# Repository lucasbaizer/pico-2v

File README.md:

# Pico 2V

Pico 2V is an [RP2350](https://www.raspberrypi.com/products/rp2350) development board that is (mostly) pin-compatible with the official [Raspberry Pi Pico 2](https://www.raspberrypi.com/products/raspberry-pi-pico-2) board, but with some additional features and changes:

* Switchable 3.3V/1.8V GPIOs: the official Pico 2 only supports running at 3.3V. Pico 2V has a jumper that lets you select between 3.3V and 1.8V.
* QSPI breakout: the official Pico 2 has an RP2350A as the chip, with on-board flash wired to the RP2350A's QSPI interface. Pico 2V has on RP2354A instead, which has 2MiB on-chip flash. As such, the RP2354A's QSPI interface on Pico 2V is broken out into two headers that can fit an [SOIC-8 breakout board](https://www.amazon.com/dp/B0DQKZG7TH) or be wired to some part of your breadboard. This allows you to write firmware that can communicate with QSPI flash using all 4 data lanes.
* On-board reset button.
* Powered-on indicator LED.
* USB-C receptacle instead of the Micro-B receptacle used on the official Pico 2.
* [10-pin Cortex Debug](https://developer.arm.com/documentation/101416/0100/Hardware-Description/Target-Interfaces/Cortex-Debug--10-pin-) connector instead of the [Raspberry Pi 3-pin Debug](https://pip-assets.raspberrypi.com/categories/885-raspberry-pi-debug-probe/documents/RP-008189-DS-1-debug-connector-specification.pdf?disposition=inline) connector used on the official Pico 2.

## Board Rendering and Pinout

* The GPIO pin headers are pin-compatible with [the official Pico 2](https://www.raspberrypi.com/documentation/microcontrollers/images/pico-2-r4-pinout.svg), and the dimensions of Pico 2V are the same as the official Pico 2, so you can easily swap out an existing Pico 2 on your breadboard for a Pico 2V. However, note that the `3V3(OUT)` pin is actually the output of the selected voltage, so it is instead a `VDD(OUT)` pin, which is only powered when a jumper is fitted to the voltage selector header. Additionally, the `3V3_EN` pin is left floating on Pico 2V.
* GPIO29 (which is not broken out/usable on the official Pico 2) is wired to an on-board voltage comparator, so you can detect from your firmware whether the RP2354A is operating at 3.3V or 1.8V by reading the value of GPIO29 (GPIO29 logic level high indicates 3.3V, logic level low indicates 1.8V). 
* The user LED is connected to GPIO25, just like on the official Pico 2.
* Pressing the `RESET` button will tie the `RUN` pin to ground.
* The QSPI pinout is as follows:
  * Pin 1: `SS` (note that pressing the `BOOTSEL` button will tie this to ground, even after the bootrom exits -- this is a fundamental constraint of how the RP235x bootrom works).
  * Pin 2: `SD1`/`MISO`
  * Pin 3: `SD2`
  * Pin 4: `GND`
  * Pin 5: `VDD` (voltage determined by voltage selection jumper)
  * Pin 6: `SD3`
  * Pin 7: `SCLK`
  * Pin 8: `SD0`/`MOSI`
  * Note that the pin numbering convention here is different from the standard SOIC-8 pin numbering convention. This is a bug with the labeling on the PCB (the '5' and '8' markers should be swapped on the PCB) that will be fixed in rev 1. However, the positions of the pins themselves does match the SOIC-8 layout; the issue is simply in the labeling of the numbers on the PCB.

## How can I buy a Pico 2V?

Fabrication exports are in the `fab/rev0` directory. I had the board produced by [JLCPCB](https://jlcpcb.com). To have JLCPCB produce some boards for you to have, zip all the files in the `fab/rev0` directory and provide the ZIP file to JLCPCB. I used Lead-Free HASL as the surface finish and a PCB thickness of 1mm. If you want them to assembly the components onto the board as well, provide them the BOM and CPL files in `fab/rev0/smt/pico-2v-bom.xls` and `fab/rev0/smt/pico-2v-all-pos.csv` respectively. Note that the GPIO and QSPI headers are not included in the BOM file, but the voltage selection header is; you can select or remove these as you desire.

## Goals for Future Revisions

* Swap the '5' and '8' markers on the QSPI breakout pins.
* Separate voltage selection jumper for QSPI.
* Two more on-board LEDs (since GPIOs 23 and 24 were left unused in rev 0).

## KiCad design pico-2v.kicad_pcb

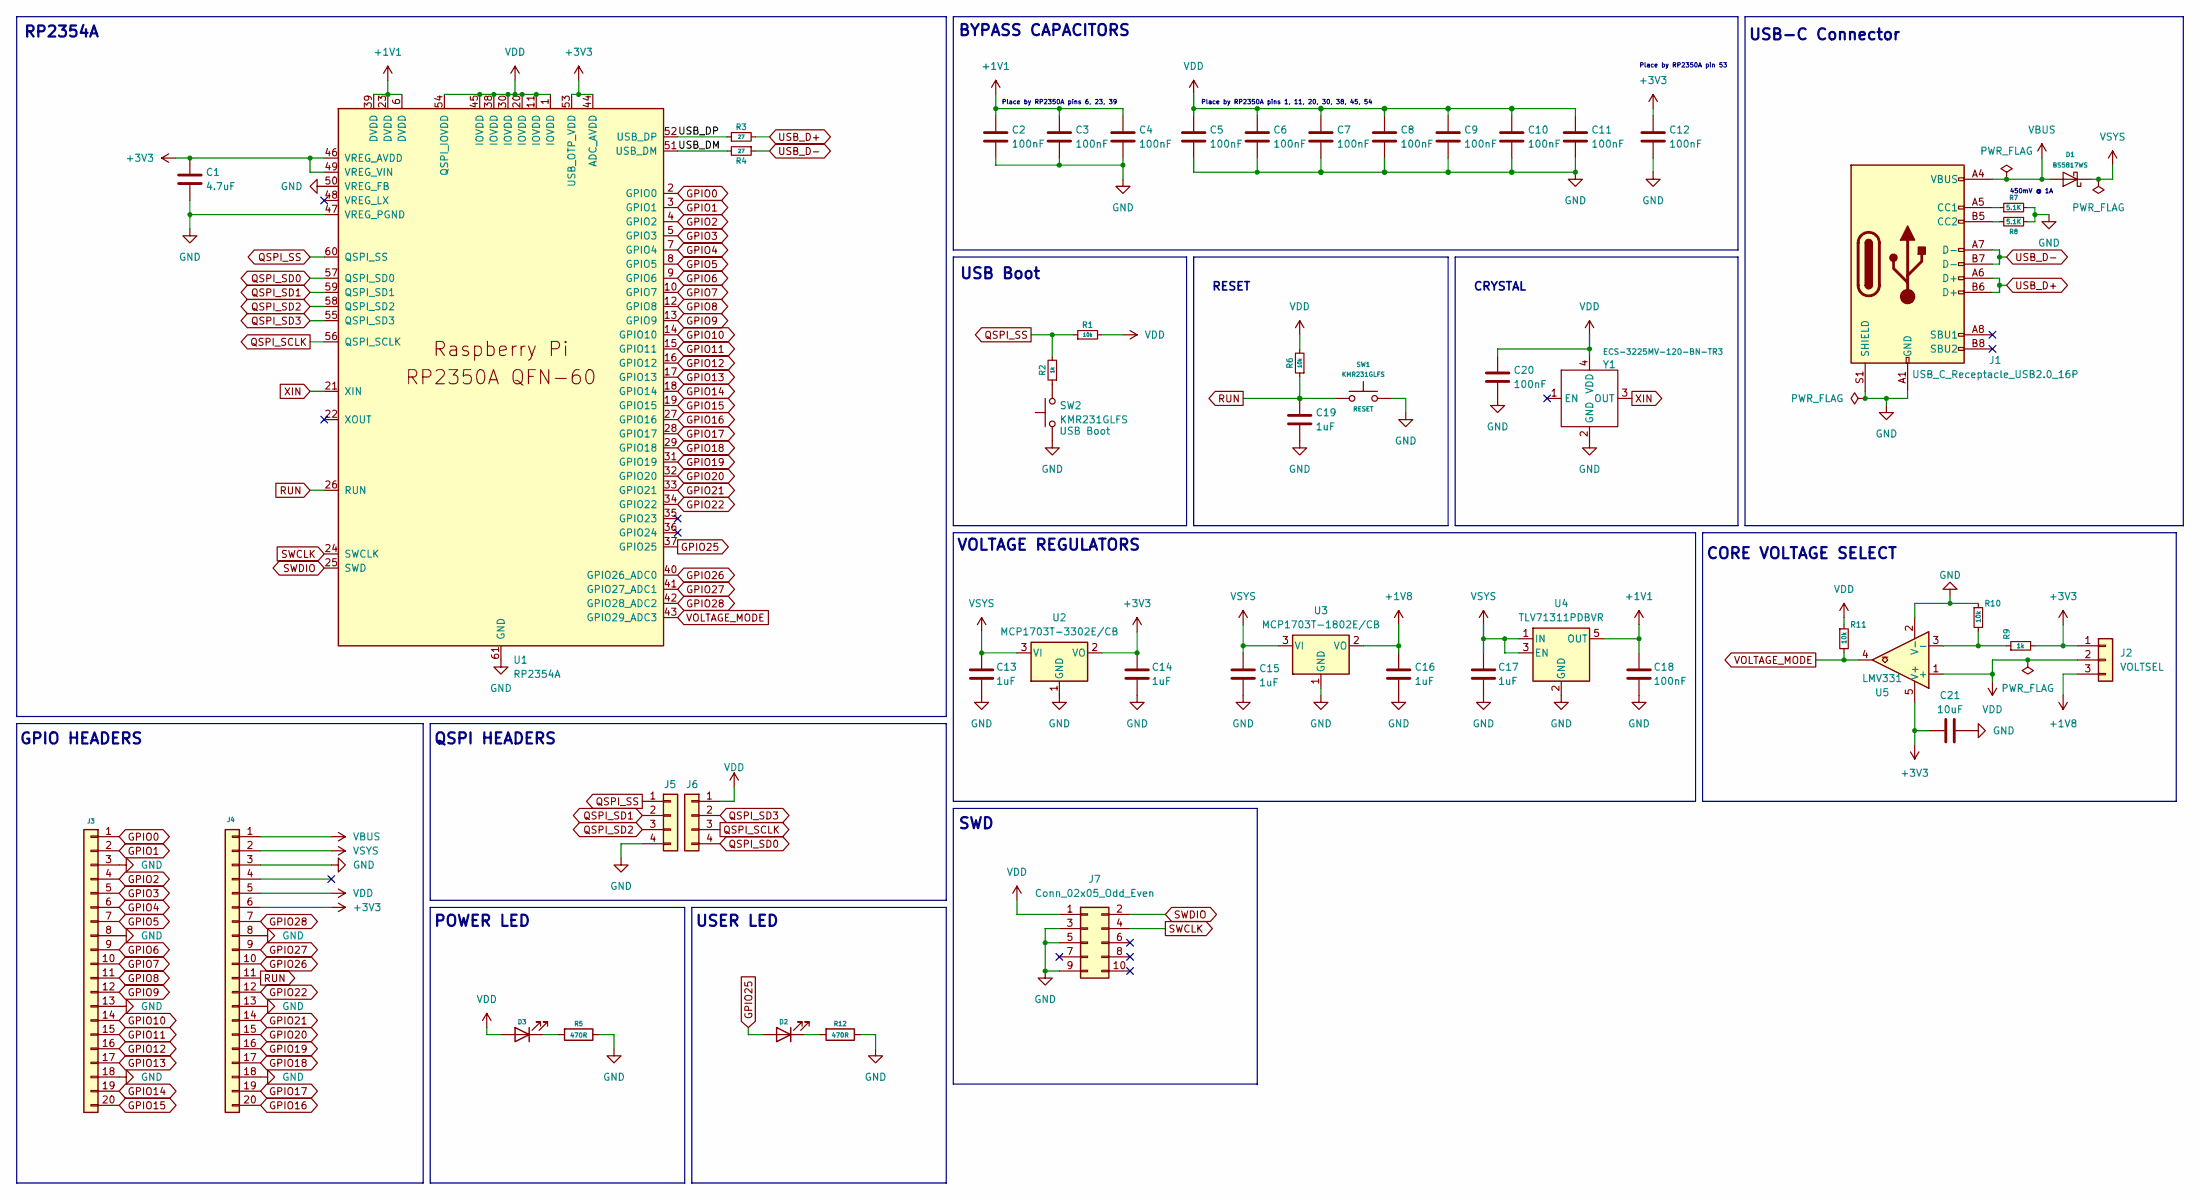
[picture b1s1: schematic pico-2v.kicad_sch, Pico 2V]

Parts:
C1: 4.7uF; C_0402_1005Metric
C2, C3, C4, C5, C6, C7, C8, C9, C10, C11, C12, C18, C20: 100nF; C_0402_1005Metric
C13, C14, C15, C16, C17, C19: 1uF; C_0402_1005Metric
C21: 10uF; C_0402_1005Metric
D1: BS5817WS; D_SOD-323_HandSoldering; MPN B5817WS
D2, D3: RED; LED_0603_1608Metric; MPN 19-21SURC/S530-A2/TR8
J1: USB_C_Receptacle_USB2.0_16P; USB_C_Receptacle_HRO_TYPE-C-31-M-12
J2: VOLTSEL; PinHeader_1x03_P2.54mm_Vertical
J3: Header-1; PinHeader_1x20_P2.54mm_Vertical; MPN DNP
J4: Header-2; PinHeader_1x20_P2.54mm_Vertical; MPN DNP
J5, J6: Conn_01x04; PinHeader_1x04_P2.54mm_Vertical
J7: Conn_02x05_Odd_Even; PinHeader_2x05_P1.27mm_Vertical_SMD
R1, R6, R10, R11: 10k; R_0402_1005Metric
R2, R9: 1k; R_0402_1005Metric
R3, R4: 27; R_0402_1005Metric
R5, R12: 470R; R_0402_1005Metric; MPN WR04X4700FTL
R7, R8: 5.1K; R_0402_1005Metric; MPN WR04X5101FTL
SW1: KMR231GLFS; SW_Push_1P1T_NO_CK_KMR2; MPN UK-B0273-SP25Y
SW2: KMR231GLFS; SW_Push_1P1T_NO_CK_KMR2
U1: RP2354A; RP2350A-QFN-60-1EP_7x7_P0.4mm_EP3.4x3.4mm_ThermalVias
U2: MCP1703T-3302E/CB; SOT-23
U3: MCP1703T-1802E/CB; SOT-23
U4: TLV71311PDBVR; SOT-23-5
U5: LMV331; SOT-353_SC-70-5
Y1: ECS-3225MV-120-BN-TR3

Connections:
+1V1: C2.1, C3.1, C4.1, C18.1, U1.6 (DVDD), U1.23 (DVDD), U1.39 (DVDD), U4.5 (OUT)
+1V8: C16.1, J2.3, U3.2 (VO)
+3V3: C1.1, C12.1, C14.1, C21.1, J2.1, J4.6, R9.2, U1.44 (ADC_AVDD), U1.46 (VREG_AVDD), U1.49 (VREG_VIN), U1.53 (USB_OTP_VDD), U2.2 (VO), U5.5 (V+)
/USB_DM: R4.2, U1.51 (USB_DM)
/USB_DP: R3.1, U1.52 (USB_DP)
GND: C1.2, C2.2, C3.2, C4.2, C5.2, C6.2, C7.2, C8.2, C9.2, C10.2, C11.2, C12.2, C13.2, C14.2, C15.2, C16.2, C17.2, C18.2, C19.2, C20.2, C21.2, J1.A1 (GND), J1.A12 (GND), J1.B1 (GND), J1.B12 (GND), J1.S1 (SHIELD), J3.3, J3.8, J3.13, J3.18, J4.3, J4.8, J4.13, J4.18, J5.4, J7.3, J7.5, J7.9, R5.1, R7.2, R8.1, R10.1, R12.1, SW1.2, SW2.1, U1.47 (VREG_PGND), U1.50 (VREG_FB), U1.61 (GND), U2.1 (GND), U3.1 (GND), U4.2 (GND), U5.2 (V-), Y1.2 (GND)
GPIO0: J3.1, U1.2 (GPIO0)
GPIO1: J3.2, U1.3 (GPIO1)
GPIO2: J3.4, U1.4 (GPIO2)
GPIO3: J3.5, U1.5 (GPIO3)
GPIO4: J3.6, U1.7 (GPIO4)
GPIO5: J3.7, U1.8 (GPIO5)
GPIO6: J3.9, U1.9 (GPIO6)
GPIO7: J3.10, U1.10 (GPIO7)
GPIO8: J3.11, U1.12 (GPIO8)
GPIO9: J3.12, U1.13 (GPIO9)
GPIO10: J3.14, U1.14 (GPIO10)
GPIO11: J3.15, U1.15 (GPIO11)
GPIO12: J3.16, U1.16 (GPIO12)
GPIO13: J3.17, U1.17 (GPIO13)
GPIO14: J3.19, U1.18 (GPIO14)
GPIO15: J3.20, U1.19 (GPIO15)
GPIO16: J4.20, U1.27 (GPIO16)
GPIO17: J4.19, U1.28 (GPIO17)
GPIO18: J4.17, U1.29 (GPIO18)
GPIO19: J4.16, U1.31 (GPIO19)
GPIO20: J4.15, U1.32 (GPIO20)
GPIO21: J4.14, U1.33 (GPIO21)
GPIO22: J4.12, U1.34 (GPIO22)
GPIO25: D2.2 (A), U1.37 (GPIO25)
GPIO26: J4.10, U1.40 (GPIO26_ADC0)
GPIO27: J4.9, U1.41 (GPIO27_ADC1)
GPIO28: J4.7, U1.42 (GPIO28_ADC2)
unnamed: D2.1 (K), R12.2
unnamed: D3.1 (K), R5.2
unnamed: J1.A5 (CC1), R7.1
unnamed: J1.B5 (CC2), R8.2
unnamed: R2.1, SW2.2
unnamed: R9.1, R10.2, U5.3 (-)
QSPI_SCLK: J6.3, U1.56 (QSPI_SCLK)
QSPI_SD0: J6.4, U1.57 (QSPI_SD0)
QSPI_SD1: J5.2, U1.59 (QSPI_SD1)
QSPI_SD2: J5.3, U1.58 (QSPI_SD2)
QSPI_SD3: J6.2, U1.55 (QSPI_SD3)
QSPI_SS: J5.1, R1.1, R2.2, U1.60 (QSPI_SS)
RUN: C19.1, J4.11, R6.1, SW1.1, U1.26 (RUN)
SWCLK: J7.4, U1.24 (SWCLK)
SWDIO: J7.2, U1.25 (SWD)
USB_D+: J1.A6 (D+), J1.B6 (D+), R3.2
USB_D-: J1.A7 (D-), J1.B7 (D-), R4.1
VBUS: D1.2 (A), J1.A4 (VBUS), J1.A9 (VBUS), J1.B4 (VBUS), J1.B9 (VBUS), J4.1
VDD: C5.1, C6.1, C7.1, C8.1, C9.1, C10.1, C11.1, C20.1, D3.2 (A), J2.2, J4.5, J6.1, J7.1, R1.2, R6.2, R11.1, U1.1 (IOVDD), U1.11 (IOVDD), U1.20 (IOVDD), U1.30 (IOVDD), U1.38 (IOVDD), U1.45 (IOVDD), U1.54 (QSPI_IOVDD), U5.1 (+), Y1.4 (VDD)
VOLTAGE_MODE: R11.2, U1.43 (GPIO29_ADC3), U5.4
VSYS: C13.1, C15.1, C17.1, D1.1 (K), J4.2, U2.3 (VI), U3.3 (VI), U4.1 (IN), U4.3 (EN)
XIN: U1.21 (XIN), Y1.3 (OUT)

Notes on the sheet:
USB Boot
RESET
CORE VOLTAGE SELECT
BYPASS CAPACITORS
CRYSTAL
RP2354A
USB-C Connector
Place by RP2350A pin 53
SWD
QSPI HEADERS
Place by RP2350A pins 6, 23, 39
VOLTAGE REGULATORS
450mV @ 1A
Place by RP2350A pins 1, 11, 20, 30, 38, 45, 54
USER LED
GPIO HEADERS
POWER LED

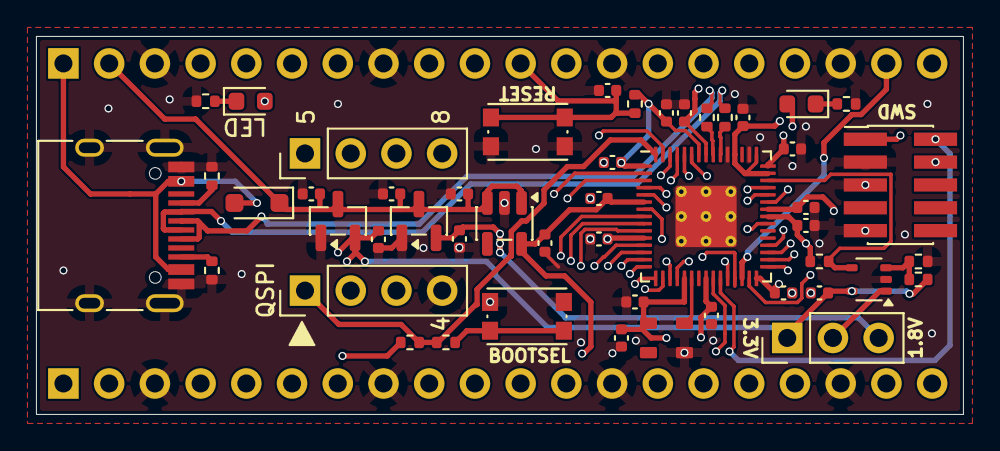
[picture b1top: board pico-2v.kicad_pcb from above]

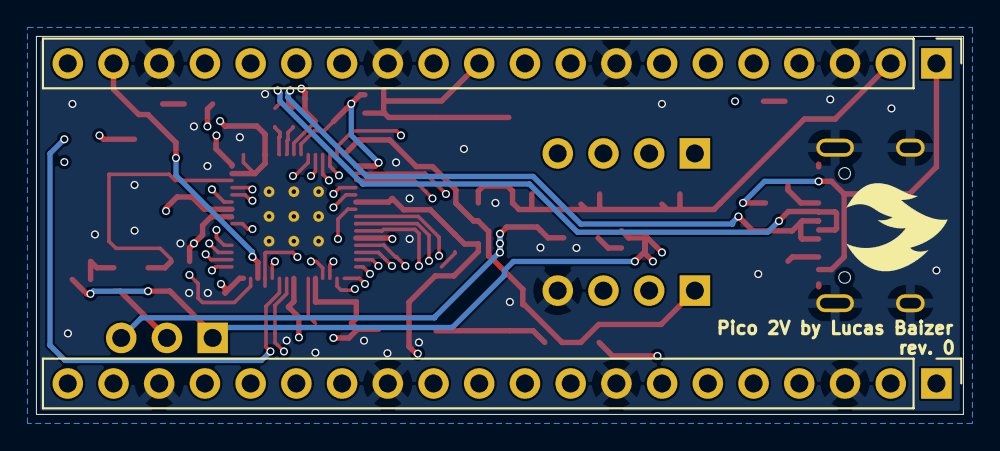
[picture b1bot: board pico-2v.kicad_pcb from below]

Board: 4 copper layers, 51.5 x 21.0 mm, 51 parts (2 on the bottom side), 55 nets.

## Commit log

2026-03-15 Stuff
2026-03-15 Bug fixes
2026-03-21 Various stuff
2026-03-21 Removed cache files
2026-03-21 Cleanup, documentation
2026-03-22 README changes
